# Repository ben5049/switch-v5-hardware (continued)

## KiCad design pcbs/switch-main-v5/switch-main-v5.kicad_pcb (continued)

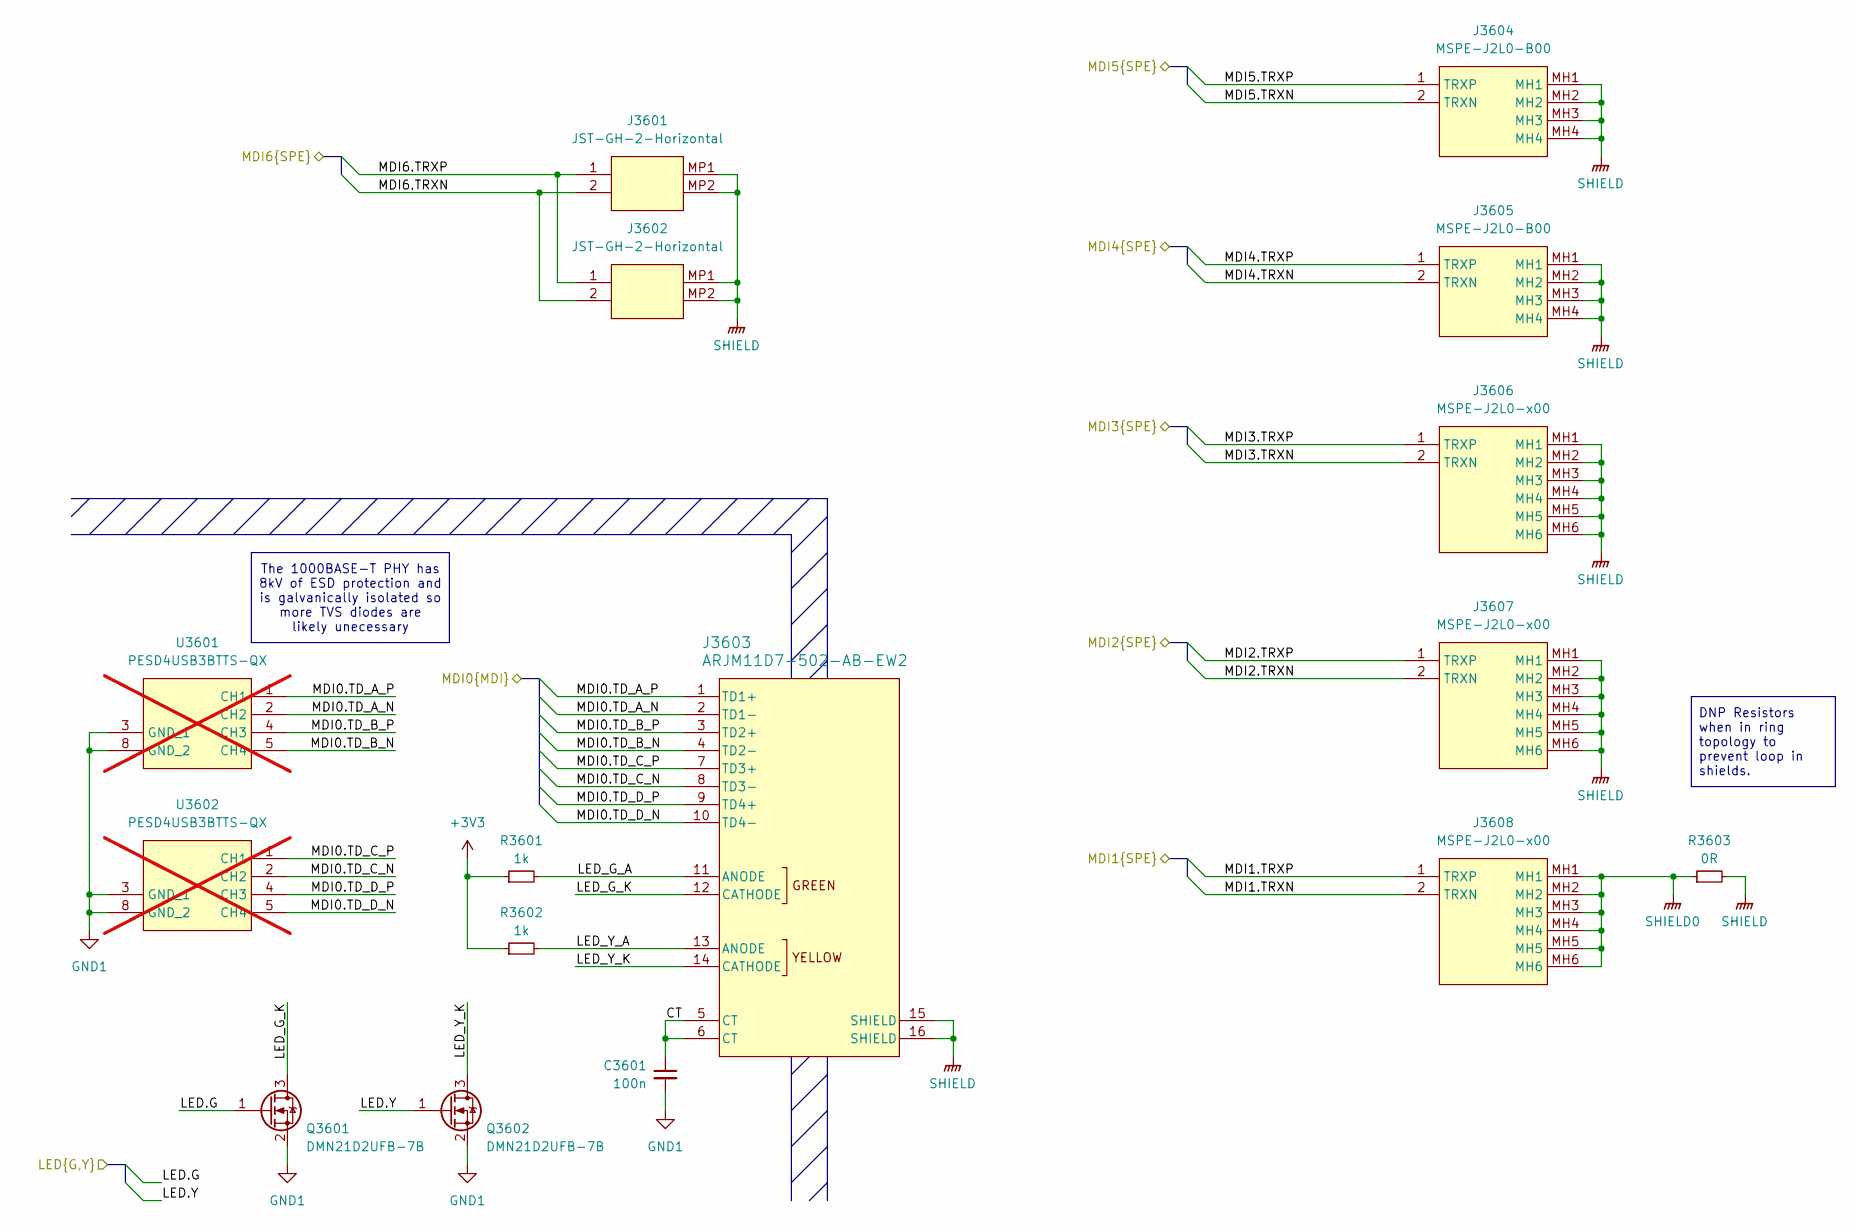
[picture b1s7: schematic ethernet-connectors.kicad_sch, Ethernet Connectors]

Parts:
C3601: 100n; C_0402
J3601, J3602: JST-GH-2-Horizontal; JST_GH_SM02B-GHS-TB_1x02-1MP_P1.25mm_Horizontal
J3603: ARJM11D7-502-AB-EW2; ARJM11D7-502-AB-EW2_ABR
J3604, J3605: MSPE-J2L0-B00; MSPEJ2L0B00; Mouser Part Number 523-MSPE-J2L0-B00
J3606, J3607, J3608: MSPE-J2L0-x00; MSPEJ2L0x00; Mouser Part Number 523-MSPE-J2L0-B00
Q3601, Q3602: DMN21D2UFB-7B; DMN21D2UFB7B; Mouser Part Number 621-DMN21D2UFB-7B
R3601, R3602: 1k; R_0402
R3603: 0R; R_0402
U3601, U3602: PESD4USB3BTTS-QX; PESD4USB3BTTSQX; Mouser Part Number 771-PESD4USB3BTTS-QX; not fitted

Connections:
+3V3: R3601.1, R3602.1; also elsewhere on the board
/CDNs & PoDL/MDI4_OUT.TRXN: J3605.2 (TRXN); also elsewhere on the board
/CDNs & PoDL/MDI4_OUT.TRXP: J3605.1 (TRXP); also elsewhere on the board
/CDNs & PoDL/MDI5_OUT.TRXN: J3604.2 (TRXN); also elsewhere on the board
/CDNs & PoDL/MDI5_OUT.TRXP: J3604.1 (TRXP); also elsewhere on the board
/CDNs & PoDL/MDI6_OUT.TRXN: J3601.2, J3602.2; also elsewhere on the board
/CDNs & PoDL/MDI6_OUT.TRXP: J3601.1, J3602.1; also elsewhere on the board
/CDNs/MDI1_OUT.TRXN: J3608.2 (TRXN); also elsewhere on the board
/CDNs/MDI1_OUT.TRXP: J3608.1 (TRXP); also elsewhere on the board
/CDNs/MDI2_OUT.TRXN: J3607.2 (TRXN); also elsewhere on the board
/CDNs/MDI2_OUT.TRXP: J3607.1 (TRXP); also elsewhere on the board
/CDNs/MDI3_OUT.TRXN: J3606.2 (TRXN); also elsewhere on the board
/CDNs/MDI3_OUT.TRXP: J3606.1 (TRXP); also elsewhere on the board
/Ethernet Connectors/CT: C3601.1, J3603.5 (CT), J3603.6 (CT)
/Ethernet Connectors/LED.G: Q3601.1 (G); also elsewhere on the board
/Ethernet Connectors/LED.Y: Q3602.1 (G); also elsewhere on the board
/Ethernet Connectors/LED_G_A: J3603.11 (ANODE), R3601.2
/Ethernet Connectors/LED_G_K: J3603.12 (CATHODE), Q3601.3 (D)
/Ethernet Connectors/LED_Y_A: J3603.13 (ANODE), R3602.2
/Ethernet Connectors/LED_Y_K: J3603.14 (CATHODE), Q3602.3 (D)
/Ethernet Connectors/MDI0.TD_A_N: J3603.2 (TD1-), U3601.2 (CH2), U3601.9 (NC); also elsewhere on the board
/Ethernet Connectors/MDI0.TD_A_P: J3603.1 (TD1+), U3601.1 (CH1), U3601.10 (NC); also elsewhere on the board
/Ethernet Connectors/MDI0.TD_B_N: J3603.4 (TD2-), U3601.5 (CH4), U3601.6 (NC); also elsewhere on the board
/Ethernet Connectors/MDI0.TD_B_P: J3603.3 (TD2+), U3601.4 (CH3), U3601.7 (NC); also elsewhere on the board
/Ethernet Connectors/MDI0.TD_C_N: J3603.8 (TD3-), U3602.2 (CH2), U3602.9 (NC); also elsewhere on the board
/Ethernet Connectors/MDI0.TD_C_P: J3603.7 (TD3+), U3602.1 (CH1), U3602.10 (NC); also elsewhere on the board
/Ethernet Connectors/MDI0.TD_D_N: J3603.10 (TD4-), U3602.5 (CH4), U3602.6 (NC); also elsewhere on the board
/Ethernet Connectors/MDI0.TD_D_P: J3603.9 (TD4+), U3602.4 (CH3), U3602.7 (NC); also elsewhere on the board
GND1: C3601.2, Q3601.2 (S), Q3602.2 (S), U3601.3 (GND_1), U3601.8 (GND_2), U3602.3 (GND_1), U3602.8 (GND_2); also elsewhere on the board
SHIELD: J3601.MP1, J3601.MP2, J3602.MP1, J3602.MP2, J3603.15 (SHIELD), J3603.16 (SHIELD), J3604.MH1, J3604.MH2, J3604.MH3, J3604.MH4, J3605.MH1, J3605.MH2, J3605.MH3, J3605.MH4, J3606.MH1, J3606.MH2, J3606.MH3, J3606.MH4, J3606.MH5, J3606.MH6, J3607.MH1, J3607.MH2, J3607.MH3, J3607.MH4, J3607.MH5, J3607.MH6, R3603.2; also elsewhere on the board
SHIELD0: J3608.MH1, J3608.MH2, J3608.MH3, J3608.MH4, J3608.MH5, J3608.MH6, R3603.1; also elsewhere on the board

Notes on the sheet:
The 1000BASE-T PHY has 8kV of ESD protection and is galvanically isolated so more TVS diodes are likely unecessary
DNP Resistors when in ring topology to prevent loop in shields.

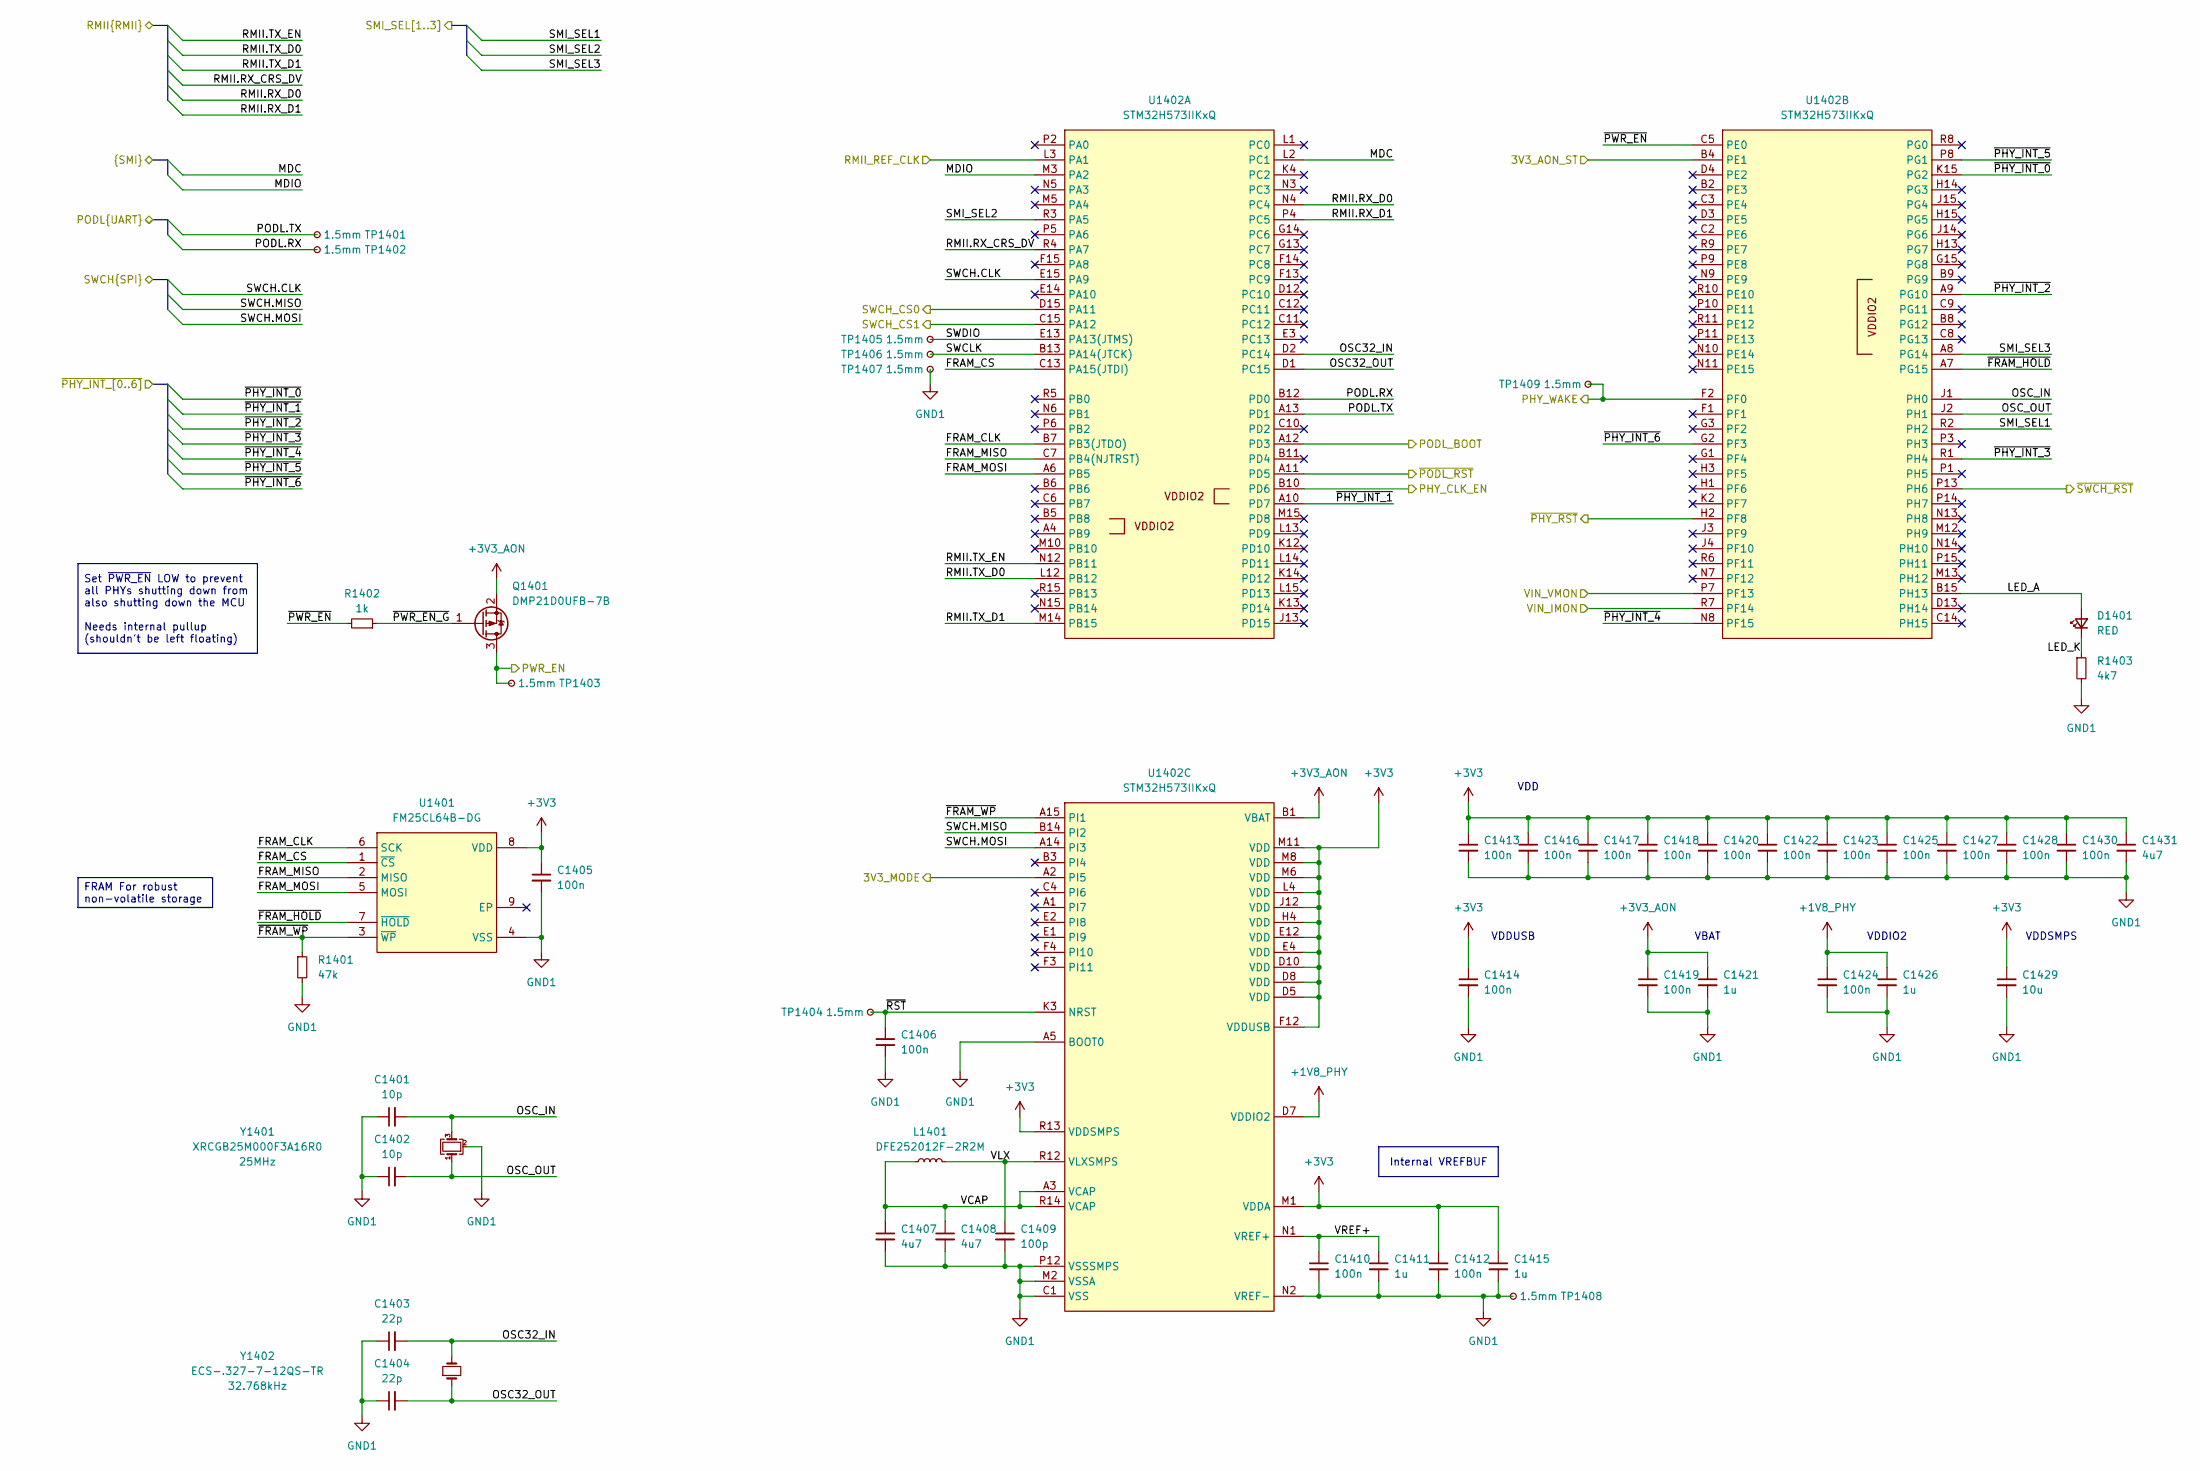
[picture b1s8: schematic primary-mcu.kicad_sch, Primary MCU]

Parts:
C1401, C1402: 10p; C_0402
C1403, C1404: 22p; C_0402
C1405, C1406, C1410, C1412, C1413, C1414, C1416, C1417, C1418, C1419, C1420, C1422, C1423, C1424, C1425, C1427, C1428, C1430: 100n; C_0402
C1407, C1408, C1431: 4u7; C_0402
C1409: 100p; C_0402
C1411, C1415, C1421, C1426: 1u; C_0402
C1429: 10u; C_0402
D1401: RED; LED_0402_1005Metric
L1401: DFE252012F-2R2M; L_1008_2520Metric
Q1401: DMP21D0UFB-7B; DMP21D0UFB7B; Mouser Part Number 621-DMP21D0UFB-7B
R1401: 47k; R_0402
R1402: 1k; R_0402
R1403: 4k7; R_0402
TP1401, TP1402, TP1403, TP1404, TP1405, TP1406, TP1407, TP1408, TP1409: 1.5mm; TestPoint_Pad_D1.5mm
U1401: FM25CL64B-DG; SON95P400X450X80-9N; Mouser Part Number 877-FM25CL64B-DG
U1402: STM32H573IIKxQ; UFBGA-201_10x10mm_Layout15x15_P0.65mm
Y1401: XRCGB25M000F3A16R0
Y1402: ECS-.327-7-12QS-TR

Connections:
+1V8_PHY: C1424.1, C1426.1, U1402.D7 (VDDIO2); also elsewhere on the board
+3V3: C1405.1, C1412.1, C1413.1, C1414.1, C1415.1, C1416.1, C1417.1, C1418.1, C1420.1, C1422.1, C1423.1, C1425.1, C1427.1, C1428.1, C1429.1, C1430.1, C1431.1, U1401.8 (VDD), U1402.D5 (VDD), U1402.D8 (VDD), U1402.D10 (VDD), U1402.E4 (VDD), U1402.E12 (VDD), U1402.F12 (VDDUSB), U1402.H4 (VDD), U1402.J12 (VDD), U1402.L4 (VDD), U1402.M1 (VDDA), U1402.M6 (VDD), U1402.M8 (VDD), U1402.M11 (VDD), U1402.R13 (VDDSMPS); also elsewhere on the board
+3V3_AON: C1419.1, C1421.1, Q1401.2 (S), U1402.B1 (VBAT); also elsewhere on the board
/Isolation Crossing/IN_C: U1402.A12 (PD3); also elsewhere on the board
/Isolation Crossing/IN_D: U1402.A11 (PD5); also elsewhere on the board
/PHYs/CLK_EN: U1402.B10 (PD6); also elsewhere on the board
/PHYs/MDC: U1402.L2 (PC1); also elsewhere on the board
/PHYs/MDIO: U1402.M3 (PA2); also elsewhere on the board
/PHYs/PWR_EN: Q1401.3 (D), TP1403.1 (1_1); also elsewhere on the board
/PHYs/SMI_SEL1: U1402.R2 (PH2); also elsewhere on the board
/PHYs/SMI_SEL2: U1402.R3 (PA5); also elsewhere on the board
/PHYs/SMI_SEL3: U1402.A8 (PG14); also elsewhere on the board
/PHYs/WAKE: TP1409.1 (1_1), U1402.F2 (PF0); also elsewhere on the board
/PHYs/~PHY_INT_0: U1402.K15 (PG2); also elsewhere on the board
/PHYs/~PHY_INT_1: U1402.A10 (PD7); also elsewhere on the board
/PHYs/~PHY_INT_2: U1402.A9 (PG10); also elsewhere on the board
/PHYs/~PHY_INT_3: U1402.R1 (PH4); also elsewhere on the board
/PHYs/~PHY_INT_4: U1402.N8 (PF15); also elsewhere on the board
/PHYs/~PHY_INT_5: U1402.P8 (PG1); also elsewhere on the board
/PHYs/~PHY_INT_6: U1402.G2 (PF3); also elsewhere on the board
/PHYs/~RST: U1402.H2 (PF8); also elsewhere on the board
/Power/3V3_AON_ST: U1402.B4 (PE1); also elsewhere on the board
/Power/3V3_MODE: U1402.A2 (PI5); also elsewhere on the board
/Power/VIN_IMON: U1402.R7 (PF14); also elsewhere on the board
/Power/VIN_VMON: U1402.P7 (PF13); also elsewhere on the board
/Primary MCU/FRAM_CLK: U1401.6 (SCK), U1402.B7 (PB3(JTDO))
/Primary MCU/FRAM_CS: U1401.1 (~CS), U1402.C13 (PA15(JTDI))
/Primary MCU/FRAM_MISO: U1401.2 (MISO), U1402.C7 (PB4(NJTRST))
/Primary MCU/FRAM_MOSI: U1401.5 (MOSI), U1402.A6 (PB5)
/Primary MCU/LED_A: D1401.2 (A), U1402.B15 (PH13)
/Primary MCU/LED_K: D1401.1 (K), R1403.1
/Primary MCU/OSC32_IN: C1403.2, U1402.D2 (PC14), Y1402.2
/Primary MCU/OSC32_OUT: C1404.2, U1402.D1 (PC15), Y1402.1
/Primary MCU/OSC_IN: C1401.2, U1402.J1 (PH0), Y1401.3
/Primary MCU/OSC_OUT: C1402.2, U1402.J2 (PH1), Y1401.1
/Primary MCU/PODL.RX: TP1402.1 (1_1), U1402.B12 (PD0); also elsewhere on the board
/Primary MCU/PODL.TX: TP1401.1 (1_1), U1402.A13 (PD1); also elsewhere on the board
/Primary MCU/RMII.RX_CRS_DV: U1402.R4 (PA7); also elsewhere on the board
/Primary MCU/RMII.RX_D0: U1402.N4 (PC4); also elsewhere on the board
/Primary MCU/RMII.RX_D1: U1402.P4 (PC5); also elsewhere on the board
/Primary MCU/RMII.TX_D0: U1402.L12 (PB12); also elsewhere on the board
/Primary MCU/RMII.TX_D1: U1402.M14 (PB15); also elsewhere on the board
/Primary MCU/RMII.TX_EN: U1402.N12 (PB11); also elsewhere on the board
/Primary MCU/RMII_REF_CLK: U1402.L3 (PA1); also elsewhere on the board
/Primary MCU/SWCH.CLK: U1402.E15 (PA9); also elsewhere on the board
/Primary MCU/SWCH.MISO: U1402.B14 (PI2); also elsewhere on the board
/Primary MCU/SWCH.MOSI: U1402.A14 (PI3); also elsewhere on the board
/Primary MCU/SWCH_CS0: U1402.D15 (PA11); also elsewhere on the board
/Primary MCU/SWCH_CS1: U1402.C15 (PA12); also elsewhere on the board
/Primary MCU/SWCLK: TP1406.1 (1_1), U1402.B13 (PA14(JTCK))
/Primary MCU/SWDIO: TP1405.1 (1_1), U1402.E13 (PA13(JTMS))
/Primary MCU/VCAP: C1407.1, C1408.1, L1401.2, U1402.A3 (VCAP), U1402.R14 (VCAP)
/Primary MCU/VLX: C1409.1, L1401.1, U1402.R12 (VLXSMPS)
/Primary MCU/VREF+: C1410.1, C1411.1, U1402.N1 (VREF+)
/Primary MCU/~FRAM_HOLD: U1401.7 (~HOLD), U1402.A7 (PG15)
/Primary MCU/~FRAM_WP: R1401.1, U1401.3 (~WP), U1402.A15 (PI1)
/Primary MCU/~PWR_EN_G: Q1401.1 (G), R1402.1
/Primary MCU/~PWR_EN: R1402.2, U1402.C5 (PE0)
/Primary MCU/~RST: C1406.1, TP1404.1 (1_1), U1402.K3 (NRST)
/Primary MCU/~SWCH_RST: U1402.P13 (PH6); also elsewhere on the board
GND1: C1401.1, C1402.1, C1403.1, C1404.1, C1405.2, C1406.2, C1407.2, C1408.2, C1409.2, C1410.2, C1411.2, C1412.2, C1413.2, C1414.2, C1415.2, C1416.2, C1417.2, C1418.2, C1419.2, C1420.2, C1421.2, C1422.2, C1423.2, C1424.2, C1425.2, C1426.2, C1427.2, C1428.2, C1429.2, C1430.2, C1431.2, R1401.2, R1403.2, TP1407.1 (1_1), TP1408.1 (1_1), U1401.4 (VSS), U1402.A5 (BOOT0), U1402.C1 (VSS), U1402.D6 (VSS), U1402.D9 (VSS), U1402.D11 (VSS), U1402.D14 (VSS), U1402.F6 (VSS), U1402.F7 (VSS), U1402.F8 (VSS), U1402.F9 (VSS), U1402.F10 (VSS), U1402.G4 (VSS), U1402.G6 (VSS), U1402.G7 (VSS), U1402.G8 (VSS), U1402.G9 (VSS), U1402.G10 (VSS), U1402.G12 (VSS), U1402.H6 (VSS), U1402.H7 (VSS), U1402.H8 (VSS), U1402.H9 (VSS), U1402.H10 (VSS), U1402.H12 (VSS), U1402.J6 (VSS), U1402.J7 (VSS), U1402.J8 (VSS), U1402.J9 (VSS), U1402.J10 (VSS), U1402.K1 (VSS), U1402.K6 (VSS), U1402.K7 (VSS), U1402.K8 (VSS), U1402.K9 (VSS), U1402.K10 (VSS), U1402.M2 (VSSA), U1402.M4 (VSS), U1402.M7 (VSS), U1402.M9 (VSS), U1402.N2 (VREF-), U1402.P12 (VSSSMPS), Y1401.2 (G), Y1401.4 (G); also elsewhere on the board

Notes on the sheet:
VBAT
VDDSMPS
VDDIO2
VDDUSB
VDD
FRAM For robust non-volatile storage
Internal VREFBUF
Set ~{PWR_EN} LOW to prevent all PHYs shutting down from also shutting down the MCU Needs internal pullup (shouldn't be left floating)

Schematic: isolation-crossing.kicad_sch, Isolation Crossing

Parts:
C3701, C3702, C3703, C3704: 100n; C_0402
U3701: ISO6521REUR; SON50P300X200X105-8N-D; Mouser Part Number 595-ISO6521REUR
U3702: ISO6520REUR; SON50P300X200X105-8N-D

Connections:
+3V3: C3701.1, C3702.1, U3701.1 (VCC1), U3702.1 (VCC1); also elsewhere on the board
+3V3_ISO: C3703.1, C3704.1, U3701.8 (VCC2), U3702.8 (VCC2); also elsewhere on the board
/Isolation Crossing/IN_C: U3702.2 (INA); also elsewhere on the board
/Isolation Crossing/IN_D: U3702.3 (INB); also elsewhere on the board
/Isolation Crossing/OUT_C: U3702.7 (OUTA); also elsewhere on the board
/Isolation Crossing/OUT_D: U3702.6 (OUTB); also elsewhere on the board
/Primary MCU/PODL.RX: U3701.2 (OUTA); also elsewhere on the board
/Primary MCU/PODL.TX: U3701.3 (INB); also elsewhere on the board
/Secondary MCU/RX: U3701.6 (OUTB); also elsewhere on the board
/Secondary MCU/TX: U3701.7 (INA); also elsewhere on the board
GND1: C3701.2, C3702.2, U3701.4 (GND1), U3702.4 (GND1); also elsewhere on the board
GND2: C3703.2, C3704.2, U3701.5 (GND2), U3702.5 (GND2); also elsewhere on the board

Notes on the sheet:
Channels C & D are default HIGH output Secondary MCU will run automatically (BOOT is inverted later)
Channels A & B are default HIGH output Prevents accidental UART transmission

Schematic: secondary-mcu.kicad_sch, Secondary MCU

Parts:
C3801, C3802, C3803, C3804: 100n; C_0402
C3805, C3806, C3807: 4u7; C_0402
Q3801, Q3802: DMN21D2UFB-7B; DMN21D2UFB7B; Mouser Part Number 621-DMN21D2UFB-7B
R3801: 47k; R_0402
R3802, R3803: 4k7; R_0402
TP3801, TP3802, TP3803, TP3804, TP3805: 1.5mm; TestPoint_Pad_D1.5mm
U3801: STM32H503KBUx; QFN-32-1EP_5x5mm_P0.5mm_EP3.45x3.45mm

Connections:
+2V5_ISO: C3803.1, C3805.1, U3801.5 (VDDA); also elsewhere on the board
+3V3_ISO: C3802.1, C3804.1, C3806.1, Q3802.1 (G), R3801.2, R3802.2, U3801.1 (VDD), U3801.17 (VDD); also elsewhere on the board
/CDNs & PoDL/PODL1.DET_EN: U3801.20 (PA9); also elsewhere on the board
/CDNs & PoDL/PODL1.DET_V+: U3801.10 (PA4); also elsewhere on the board
/CDNs & PoDL/PODL1.EN: U3801.19 (PA8); also elsewhere on the board
/CDNs & PoDL/PODL1.IMON: U3801.9 (PA3); also elsewhere on the board
/CDNs & PoDL/PODL2.DET_EN: U3801.2 (PC14); also elsewhere on the board
/CDNs & PoDL/PODL2.DET_V+: U3801.15 (PB1); also elsewhere on the board
/CDNs & PoDL/PODL2.EN: U3801.22 (PA12); also elsewhere on the board
/CDNs & PoDL/PODL2.IMON: U3801.12 (PA6); also elsewhere on the board
/CDNs & PoDL/PODL3.DET_EN: U3801.29 (PB6); also elsewhere on the board
/CDNs & PoDL/PODL3.DET_V+: U3801.14 (PB0); also elsewhere on the board
/CDNs & PoDL/PODL3.EN: U3801.30 (PB7); also elsewhere on the board
/CDNs & PoDL/PODL3.IMON: U3801.13 (PA7); also elsewhere on the board
/CDNs & PoDL/PODL_DIAG_EN: U3801.21 (PA11); also elsewhere on the board
/Isolation Crossing/OUT_C: Q3801.1 (G); also elsewhere on the board
/Isolation Crossing/OUT_D: Q3802.3 (D); also elsewhere on the board
/Power/2V5_ISO_EN: U3801.7 (PA1); also elsewhere on the board
/Power/3V3_ISO_MODE: U3801.28 (PB5); also elsewhere on the board
/Power/VIN_ISO_IMON: U3801.6 (PA0); also elsewhere on the board
/Power/VIN_ISO_VMON: U3801.8 (PA2); also elsewhere on the board
/Secondary MCU/NRST: C3801.1, R3803.1, TP3804.1 (1_1), U3801.4 (NRST)
/Secondary MCU/RX: U3801.25 (PA15(JTDI)); also elsewhere on the board
/Secondary MCU/SWCLK: TP3802.1 (1_1), U3801.24 (PA14(JTCK))
/Secondary MCU/SWDIO: TP3801.1 (1_1), U3801.23 (PA13(JTMS))
/Secondary MCU/TX: U3801.11 (PA5); also elsewhere on the board
/Secondary MCU/VCAP: C3807.1, U3801.16 (VCAP)
/Secondary MCU/~BOOT: Q3801.3 (D), R3801.1, TP3805.1 (1_1), U3801.31 (BOOT0)
/Secondary MCU/~RST_OD: Q3802.2 (S), R3802.1, R3803.2
GND2: C3801.2, C3802.2, C3803.2, C3804.2, C3805.2, C3806.2, C3807.2, Q3801.2 (S), TP3803.1 (1_1), U3801.33 (VSS); also elsewhere on the board

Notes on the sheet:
Invert BOOT so it is LOW by default (flash boot)
Convert ~{RST} from a push-pull signal to an open drain signal (without inversion)

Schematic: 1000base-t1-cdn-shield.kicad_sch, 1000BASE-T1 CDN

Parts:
C3301: 100n; C_0402
C3302: 100n; C_0603; Voltage 100V
C3303: 1n; C_0805; Voltage 1kV
D3301: 824012823; Mouser Part Number 710-824012823
D3302, D3303: SZESD7241N2T5G; SZESD7462N2T5G; Mouser Part Number 863-SZESD7241N2T5G
FL3301: ACT1210G-800-2P-TL10; ACT1210G; Mouser Part Number 810-ACT1210G8002PTL1
R3301: 100R; R_0402
T3301: 74930100

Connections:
/CDNs/1000BASE-T1 CDN 1/CTP: C3301.1, T3301.5 (PM)
/CDNs/1000BASE-T1 CDN 1/CTS1: C3302.2, T3301.4 (OUT1B)
/CDNs/1000BASE-T1 CDN 1/CTS2: C3302.1, R3301.2, T3301.3 (OUT2A)
/CDNs/1000BASE-T1 CDN 1/TERM: C3303.1, R3301.1
/CDNs/1000BASE-T1 CDN 1/TRXN: FL3301.2, T3301.2 (IN-)
/CDNs/1000BASE-T1 CDN 1/TRXP: FL3301.1, T3301.1 (IN+)
/CDNs/MDI1_IN.TRXN: D3301.1, D3301.6, FL3301.3; also elsewhere on the board
/CDNs/MDI1_IN.TRXP: D3301.2, D3301.5, FL3301.4; also elsewhere on the board
/CDNs/MDI1_OUT.TRXN: D3303.2 (A2), T3301.7 (OUT2B); also elsewhere on the board
/CDNs/MDI1_OUT.TRXP: D3302.2 (A2), T3301.6 (OUT1A); also elsewhere on the board
GND1: C3301.2, D3301.3, D3301.4; also elsewhere on the board
SHIELD0: C3303.2, D3302.1 (A1), D3303.1 (A1); also elsewhere on the board

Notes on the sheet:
Termination
ESD Protection
CMC

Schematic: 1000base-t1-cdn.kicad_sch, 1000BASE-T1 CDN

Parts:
C3401: 100n; C_0402
C3402: 100n; C_0603; Voltage 100V
C3403: 1n; C_0805; Voltage 1kV
D3401: 824012823; Mouser Part Number 710-824012823
D3402, D3403: SZESD7241N2T5G; SZESD7462N2T5G; Mouser Part Number 863-SZESD7241N2T5G
FL3401: ACT1210G-800-2P-TL10; ACT1210G; Mouser Part Number 810-ACT1210G8002PTL1
R3401: 100R; R_0402
T3401: 74930100

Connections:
/CDNs/1000BASE-T1 CDN 2/CTP: C3401.1, T3401.5 (PM)
/CDNs/1000BASE-T1 CDN 2/CTS1: C3402.2, T3401.4 (OUT1B)
/CDNs/1000BASE-T1 CDN 2/CTS2: C3402.1, R3401.2, T3401.3 (OUT2A)
/CDNs/1000BASE-T1 CDN 2/TERM: C3403.1, R3401.1
/CDNs/1000BASE-T1 CDN 2/TRXN: FL3401.2, T3401.2 (IN-)
/CDNs/1000BASE-T1 CDN 2/TRXP: FL3401.1, T3401.1 (IN+)
/CDNs/MDI2_IN.TRXN: D3401.1, D3401.6, FL3401.3; also elsewhere on the board
/CDNs/MDI2_IN.TRXP: D3401.2, D3401.5, FL3401.4; also elsewhere on the board
/CDNs/MDI2_OUT.TRXN: D3403.2 (A2), T3401.7 (OUT2B); also elsewhere on the board
/CDNs/MDI2_OUT.TRXP: D3402.2 (A2), T3401.6 (OUT1A); also elsewhere on the board
GND1: C3401.2, D3401.3, D3401.4; also elsewhere on the board
SHIELD: C3403.2, D3402.1 (A1), D3403.1 (A1); also elsewhere on the board

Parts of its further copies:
C3501: 100n; C_0402
C3502: 100n; C_0603; Voltage 100V
C3503: 1n; C_0805; Voltage 1kV
D3501: 824012823; Mouser Part Number 710-824012823
D3502, D3503: SZESD7241N2T5G; SZESD7462N2T5G; Mouser Part Number 863-SZESD7241N2T5G
FL3501: ACT1210G-800-2P-TL10; ACT1210G; Mouser Part Number 810-ACT1210G8002PTL1
R3501: 100R; R_0402
T3501: 74930100

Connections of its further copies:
/CDNs/1000BASE-T1 CDN 3/CTP: C3501.1, T3501.5 (PM)
/CDNs/1000BASE-T1 CDN 3/CTS1: C3502.2, T3501.4 (OUT1B)
/CDNs/1000BASE-T1 CDN 3/CTS2: C3502.1, R3501.2, T3501.3 (OUT2A)
/CDNs/1000BASE-T1 CDN 3/TERM: C3503.1, R3501.1
/CDNs/1000BASE-T1 CDN 3/TRXN: FL3501.2, T3501.2 (IN-)
/CDNs/1000BASE-T1 CDN 3/TRXP: FL3501.1, T3501.1 (IN+)
/CDNs/MDI3_IN.TRXN: D3501.1, D3501.6, FL3501.3; also elsewhere on the board
/CDNs/MDI3_IN.TRXP: D3501.2, D3501.5, FL3501.4; also elsewhere on the board
/CDNs/MDI3_OUT.TRXN: D3503.2 (A2), T3501.7 (OUT2B); also elsewhere on the board
/CDNs/MDI3_OUT.TRXP: D3502.2 (A2), T3501.6 (OUT1A); also elsewhere on the board
GND1: C3501.2, D3501.3, D3501.4; also elsewhere on the board
SHIELD: C3503.2, D3502.1 (A1), D3503.1 (A1); also elsewhere on the board

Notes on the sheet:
Termination
ESD Protection
CMC

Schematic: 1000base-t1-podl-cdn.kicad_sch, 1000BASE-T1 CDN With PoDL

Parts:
C2701: 100n; C_0402
C2702: 100n; C_0603; Voltage 100V
C2703: 1n; C_0805; Voltage 1kV
D2701: 824012823; Mouser Part Number 710-824012823
D2702, D2703: SZESD7241N2T5G; SZESD7462N2T5G; Mouser Part Number 863-SZESD7241N2T5G
FL2701: ACT1210G-800-2P-TL10; ACT1210G; Mouser Part Number 810-ACT1210G8002PTL1
L2701, L2702: ADL3225VT-4R7M-TL000; ADL3225VT4R7MTL000; Mouser Part Number 810-ADL3225VT4R7MTL0
R2701: 100R; R_0402
T2701: 74930100

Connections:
/CDNs & PoDL/1000BASE-T1 PoDL CDN 1/CTP: C2701.1, T2701.5 (PM)
/CDNs & PoDL/1000BASE-T1 PoDL CDN 1/CTS1: C2702.2, T2701.4 (OUT1B)
/CDNs & PoDL/1000BASE-T1 PoDL CDN 1/CTS2: C2702.1, R2701.2, T2701.3 (OUT2A)
/CDNs & PoDL/1000BASE-T1 PoDL CDN 1/PWR+: L2702.3, L2702.4; also elsewhere on the board
/CDNs & PoDL/1000BASE-T1 PoDL CDN 1/TERM: C2703.1, R2701.1
/CDNs & PoDL/1000BASE-T1 PoDL CDN 1/TRXN: FL2701.2, T2701.2 (IN-)
/CDNs & PoDL/1000BASE-T1 PoDL CDN 1/TRXP: FL2701.1, T2701.1 (IN+)
/CDNs & PoDL/MDI4_IN.TRXN: D2701.1, D2701.6, FL2701.3; also elsewhere on the board
/CDNs & PoDL/MDI4_IN.TRXP: D2701.2, D2701.5, FL2701.4; also elsewhere on the board
/CDNs & PoDL/MDI4_OUT.TRXN: D2703.2 (A2), L2701.1, L2701.2, T2701.7 (OUT2B); also elsewhere on the board
/CDNs & PoDL/MDI4_OUT.TRXP: D2702.2 (A2), L2702.1, L2702.2, T2701.6 (OUT1A); also elsewhere on the board
GND1: C2701.2, D2701.3, D2701.4; also elsewhere on the board
GND2: L2701.3, L2701.4; also elsewhere on the board
SHIELD: C2703.2, D2702.1 (A1), D2703.1 (A1); also elsewhere on the board

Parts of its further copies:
C2801: 100n; C_0402
C2802: 100n; C_0603; Voltage 100V
C2803: 1n; C_0805; Voltage 1kV
D2801: 824012823; Mouser Part Number 710-824012823
D2802, D2803: SZESD7241N2T5G; SZESD7462N2T5G; Mouser Part Number 863-SZESD7241N2T5G
FL2801: ACT1210G-800-2P-TL10; ACT1210G; Mouser Part Number 810-ACT1210G8002PTL1
L2801, L2802: ADL3225VT-4R7M-TL000; ADL3225VT4R7MTL000; Mouser Part Number 810-ADL3225VT4R7MTL0
R2801: 100R; R_0402
T2801: 74930100

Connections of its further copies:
/CDNs & PoDL/1000BASE-T1 PoDL CDN 2/CTP: C2801.1, T2801.5 (PM)
/CDNs & PoDL/1000BASE-T1 PoDL CDN 2/CTS1: C2802.2, T2801.4 (OUT1B)
/CDNs & PoDL/1000BASE-T1 PoDL CDN 2/CTS2: C2802.1, R2801.2, T2801.3 (OUT2A)
/CDNs & PoDL/1000BASE-T1 PoDL CDN 2/PWR+: L2802.3, L2802.4; also elsewhere on the board
/CDNs & PoDL/1000BASE-T1 PoDL CDN 2/TERM: C2803.1, R2801.1
/CDNs & PoDL/1000BASE-T1 PoDL CDN 2/TRXN: FL2801.2, T2801.2 (IN-)
/CDNs & PoDL/1000BASE-T1 PoDL CDN 2/TRXP: FL2801.1, T2801.1 (IN+)
/CDNs & PoDL/MDI5_IN.TRXN: D2801.1, D2801.6, FL2801.3; also elsewhere on the board
/CDNs & PoDL/MDI5_IN.TRXP: D2801.2, D2801.5, FL2801.4; also elsewhere on the board
/CDNs & PoDL/MDI5_OUT.TRXN: D2803.2 (A2), L2801.1, L2801.2, T2801.7 (OUT2B); also elsewhere on the board
/CDNs & PoDL/MDI5_OUT.TRXP: D2802.2 (A2), L2802.1, L2802.2, T2801.6 (OUT1A); also elsewhere on the board
GND1: C2801.2, D2801.3, D2801.4; also elsewhere on the board
GND2: L2801.3, L2801.4; also elsewhere on the board
SHIELD: C2803.2, D2802.1 (A1), D2803.1 (A1); also elsewhere on the board

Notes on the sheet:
CMC
2x 100mΩ 720mA Max
Can also use LQH32NH3R3J23L
Termination
ESD Protection

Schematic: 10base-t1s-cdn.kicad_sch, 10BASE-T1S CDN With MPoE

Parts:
C2901: 100n; C_0402
C2902: 100n; C_0603; Voltage 100V
C2903: 1n; C_0805; Voltage 1kV
D2901: 824012823; Mouser Part Number 710-824012823
D2902, D2903: SZESD7241N2T5G; SZESD7462N2T5G; Mouser Part Number 863-SZESD7241N2T5G
FL2901: ACT1210E-131-2P-TL00; ACT1210E; Mouser Part Number 810-ACT1210E1312PTL0
L2901: MSD7342-333MLC_DM; MSD7342
L2902: MSD7342-333MLC; MSD7342
R2901: 3k3; R_0402
T2901: 74930100

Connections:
/CDNs & PoDL/10BASE-T1S CDN/CTP: C2901.1, T2901.5 (PM)
/CDNs & PoDL/10BASE-T1S CDN/CTS1: C2902.2, T2901.4 (OUT1B)
/CDNs & PoDL/10BASE-T1S CDN/CTS2: C2902.1, R2901.2, T2901.3 (OUT2A)
/CDNs & PoDL/10BASE-T1S CDN/MDI_PWR+: L2901.4 (2), L2902.3
/CDNs & PoDL/10BASE-T1S CDN/MDI_PWR-: L2901.1, L2902.4 (2)
/CDNs & PoDL/10BASE-T1S CDN/PWR+: L2902.1; also elsewhere on the board
/CDNs & PoDL/10BASE-T1S CDN/TERM: C2903.1, R2901.1
/CDNs & PoDL/10BASE-T1S CDN/TRXN: FL2901.2, T2901.2 (IN-)
/CDNs & PoDL/10BASE-T1S CDN/TRXP: FL2901.1, T2901.1 (IN+)
/CDNs & PoDL/MDI6_IN.TRXN: D2901.1, D2901.6, FL2901.3; also elsewhere on the board
/CDNs & PoDL/MDI6_IN.TRXP: D2901.2, D2901.5, FL2901.4; also elsewhere on the board
/CDNs & PoDL/MDI6_OUT.TRXN: D2903.2 (A2), L2901.3, T2901.7 (OUT2B); also elsewhere on the board
/CDNs & PoDL/MDI6_OUT.TRXP: D2902.2 (A2), L2901.2 (4), T2901.6 (OUT1A); also elsewhere on the board
GND1: C2901.2, D2901.3, D2901.4; also elsewhere on the board
GND2: L2902.2 (4); also elsewhere on the board
SHIELD: C2903.2, D2902.1 (A1), D2903.1 (A1); also elsewhere on the board

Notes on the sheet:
ESD Protection
Change termination resistor to 100Ω for end node
CMC
Termination
4x 270mΩ 760mA Max

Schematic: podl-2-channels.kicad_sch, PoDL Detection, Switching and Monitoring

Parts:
C3001, C3002: 100n; C_0402
D3001, D3002: PMEG4002EL-QYL
Q3001, Q3002, Q3004, Q3006: DMP21D0UFB-7B; DMP21D0UFB7B; Mouser Part Number 621-DMP21D0UFB-7B
Q3003, Q3005: DMN21D2UFB-7B; DMN21D2UFB7B; Mouser Part Number 621-DMN21D2UFB-7B
R3001, R3002, R3003, R3004, R3013, R3014, R3015, R3016: 4k7; R_0402
R3005: 470R; R_0402
R3006, R3010, R3017, R3021: 2k2; R_0402
R3007, R3009, R3012, R3018, R3020, R3023: 10k; R_0402
R3008, R3019: 1k; R_0402
R3011, R3022: 100k; R_0402
U3001, U3002: TPS27S100BRRK; TPS27S100ARRKR
Z3001, Z3002: BZX884-C3V3,315; BZX884; Mouser Part Number 771-BZX884-C3V9315

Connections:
+6V5_ISO: Q3001.2 (S), Q3002.2 (S), R3009.1, R3020.1; also elsewhere on the board
+VIN_ISO: U3001.9 (IN), U3001.10 (IN), U3001.11 (IN), U3001.12 (IN), U3002.9 (IN), U3002.10 (IN), U3002.11 (IN), U3002.12 (IN); also elsewhere on the board
/CDNs & PoDL/1000BASE-T1 PoDL CDN 1/PWR+: D3001.1 (K), R3011.1, U3001.5 (OUT), U3001.6 (OUT), U3001.7 (OUT), U3001.8 (OUT); also elsewhere on the board
/CDNs & PoDL/1000BASE-T1 PoDL CDN 2/PWR+: D3002.1 (K), R3022.1, U3002.5 (OUT), U3002.6 (OUT), U3002.7 (OUT), U3002.8 (OUT); also elsewhere on the board
/CDNs & PoDL/PODL1.DET_EN: R3007.1, R3008.1; also elsewhere on the board
/CDNs & PoDL/PODL1.DET_V+: R3011.2, R3012.1, Z3001.1 (K); also elsewhere on the board
/CDNs & PoDL/PODL1.EN: R3002.1; also elsewhere on the board
/CDNs & PoDL/PODL1.IMON: C3001.1, R3001.2, R3004.1; also elsewhere on the board
/CDNs & PoDL/PODL2.DET_EN: R3018.1, R3019.1; also elsewhere on the board
/CDNs & PoDL/PODL2.DET_V+: R3022.2, R3023.1, Z3002.1 (K); also elsewhere on the board
/CDNs & PoDL/PODL2.EN: R3014.1; also elsewhere on the board
/CDNs & PoDL/PODL2.IMON: C3002.1, R3013.2, R3016.1; also elsewhere on the board
/CDNs & PoDL/PODL_DIAG_EN: R3003.1, R3015.1; also elsewhere on the board
/CDNs & PoDL/PoDL (2 Channels)/CURRENT_MIRROR_GATE: Q3001.1 (G), Q3001.3 (D), Q3002.1 (G), R3005.1
/CDNs & PoDL/PoDL (2 Channels)/CURRENT_MIRROR_OUT: Q3002.3 (D), Q3004.2 (S), Q3006.2 (S)
/CDNs & PoDL/PoDL (2 Channels)/DIAG_EN1: R3003.2, U3001.14 (DIAG_EN)
/CDNs & PoDL/PoDL (2 Channels)/DIAG_EN2: R3015.2, U3002.14 (DIAG_EN)
/CDNs & PoDL/PoDL (2 Channels)/EN1: R3002.2, U3001.3 (EN)
/CDNs & PoDL/PoDL (2 Channels)/EN2: R3014.2, U3002.3 (EN)
/CDNs & PoDL/PoDL (2 Channels)/G1: Q3003.1 (G), R3008.2
/CDNs & PoDL/PoDL (2 Channels)/G2: Q3003.3 (D), Q3004.1 (G), R3009.2
/CDNs & PoDL/PoDL (2 Channels)/G3: Q3005.1 (G), R3019.2
/CDNs & PoDL/PoDL (2 Channels)/G4: Q3005.3 (D), Q3006.1 (G), R3020.2
/CDNs & PoDL/PoDL (2 Channels)/ILIM1: R3010.2, U3001.15 (ILIM)
/CDNs & PoDL/PoDL (2 Channels)/ILIM2: R3021.2, U3002.15 (ILIM)
/CDNs & PoDL/PoDL (2 Channels)/IMON1: R3004.2, R3006.2, U3001.16 (IMON)
/CDNs & PoDL/PoDL (2 Channels)/IMON2: R3016.2, R3017.2, U3002.16 (IMON)
/CDNs & PoDL/PoDL (2 Channels)/I_PODL1: D3001.2 (A), Q3004.3 (D)
/CDNs & PoDL/PoDL (2 Channels)/I_PODL2: D3002.2 (A), Q3006.3 (D)
GND2: C3001.2, C3002.2, Q3003.2 (S), Q3005.2 (S), R3001.1, R3005.2, R3006.1, R3007.2, R3010.1, R3012.2, R3013.1, R3017.1, R3018.2, R3021.1, R3023.2, U3001.2 (GND), U3001.17 (EP), U3002.2 (GND), U3002.17 (EP), Z3001.2 (A), Z3002.2 (A); also elsewhere on the board

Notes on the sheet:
Power Switch 2
Current Source (Mirror)
Current Switches
Power Switch 1
1.1A Maximum output current 1.1A Maximum measurable current
If the output is shorted the current is still limited to 14mA, and 91mW will be dissapated (in spec)
Each channel can be enabled individually to check for PoDL devices. Since the outputs share a current source, only one channel can be checked at a time.
I_{OUT} = 0.28046 * V_{MON}
6.5 / 470 = ~14mA Within the 9-16mA PoDL spec
1/11 Potential divider and zener clamp to protect the 3V3 microcontroller IO.
During the detection phase, 9-16mA is sent into TRXP and the resulting voltage is measured. If a PoDL compatible device is detected on the other end (indicated by a 4.05-4.55V zener diode) then the full 24V is enabled.
IMON can go up to 4.75V, potential divider limits this to be withing 2.5V ADC range.

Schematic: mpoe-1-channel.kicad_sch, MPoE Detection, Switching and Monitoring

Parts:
C3101, C3102: 100n; C_0402
D3101: PMEG4002EL-QYL
F3101: 0603L008YR; Fuse_0603_1608Metric
Q3101: DMN21D2UFB-7B; DMN21D2UFB7B; Mouser Part Number 621-DMN21D2UFB-7B
Q3102: DMP21D0UFB-7B; DMP21D0UFB7B; Mouser Part Number 621-DMP21D0UFB-7B
R3101: 10k; R_0402
R3102: 1k; R_0402
R3103: 100k; R_0402
R3104, R3106, R3107, R3108: 4k7; R_0402
R3105: 1R; R_0402
R3109, R3110: 2k2; R_0402
U3101: NCS213RMUTAG; Mouser Part Number 863-NCS213RMUTAG
U3102: TPS27S100BRRK; TPS27S100ARRKR

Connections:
+2V5_ISO: C3102.2, U3101.6 (VS); also elsewhere on the board
+6V5_ISO: Q3102.2 (S), R3103.2; also elsewhere on the board
+VIN_ISO: U3102.9 (IN), U3102.10 (IN), U3102.11 (IN), U3102.12 (IN); also elsewhere on the board
/CDNs & PoDL/10BASE-T1S CDN/PWR+: D3101.1 (K), U3102.5 (OUT), U3102.6 (OUT), U3102.7 (OUT), U3102.8 (OUT); also elsewhere on the board
/CDNs & PoDL/MPoE (1 Channel)/DET: Q3101.1 (G), R3102.1
/CDNs & PoDL/MPoE (1 Channel)/DET+: Q3102.3 (D), R3105.1, U3101.2 (IN+), U3101.3 (IN+)
/CDNs & PoDL/MPoE (1 Channel)/DET-: F3101.2, R3105.2, U3101.4 (IN-), U3101.5 (IN-)
/CDNs & PoDL/MPoE (1 Channel)/DET_FUSED: D3101.2 (A), F3101.1
/CDNs & PoDL/MPoE (1 Channel)/DIAG_EN: R3107.2, U3102.14 (DIAG_EN)
/CDNs & PoDL/MPoE (1 Channel)/EN: R3106.2, U3102.3 (EN)
/CDNs & PoDL/MPoE (1 Channel)/ILIM: R3110.2, U3102.15 (ILIM)
/CDNs & PoDL/MPoE (1 Channel)/IMON: R3108.2, R3109.2, U3102.16 (IMON)
/CDNs & PoDL/MPoE (1 Channel)/~DET: Q3101.3 (D), Q3102.1 (G), R3103.1
/CDNs & PoDL/PODL3.DET_EN: R3101.2, R3102.2; also elsewhere on the board
/CDNs & PoDL/PODL3.DET_V+: U3101.10 (OUT); also elsewhere on the board
/CDNs & PoDL/PODL3.EN: R3106.1; also elsewhere on the board
/CDNs & PoDL/PODL3.IMON: C3101.1, R3104.2, R3108.1; also elsewhere on the board
/CDNs & PoDL/PODL_DIAG_EN: R3107.1; also elsewhere on the board
GND2: C3101.2, C3102.1, Q3101.2 (S), R3101.1, R3104.1, R3109.1, R3110.1, U3101.8 (REF), U3101.9 (GND), U3102.2 (GND), U3102.17 (EP); also elsewhere on the board

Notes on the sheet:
IMON can go up to 4.75V, potential divider limits this to be withing 2.5V ADC range.
Fuse protects against short circuit output
During detection, the bus is powered at 6.5V, and each PD draws 1mA for every watt they require. This is detected as a voltage drop across the 1 ohm resistor.
1.1A Maximum output current 1.1A Maximum measurable current
I_{OUT} = 0.28046 * V_{MON}
